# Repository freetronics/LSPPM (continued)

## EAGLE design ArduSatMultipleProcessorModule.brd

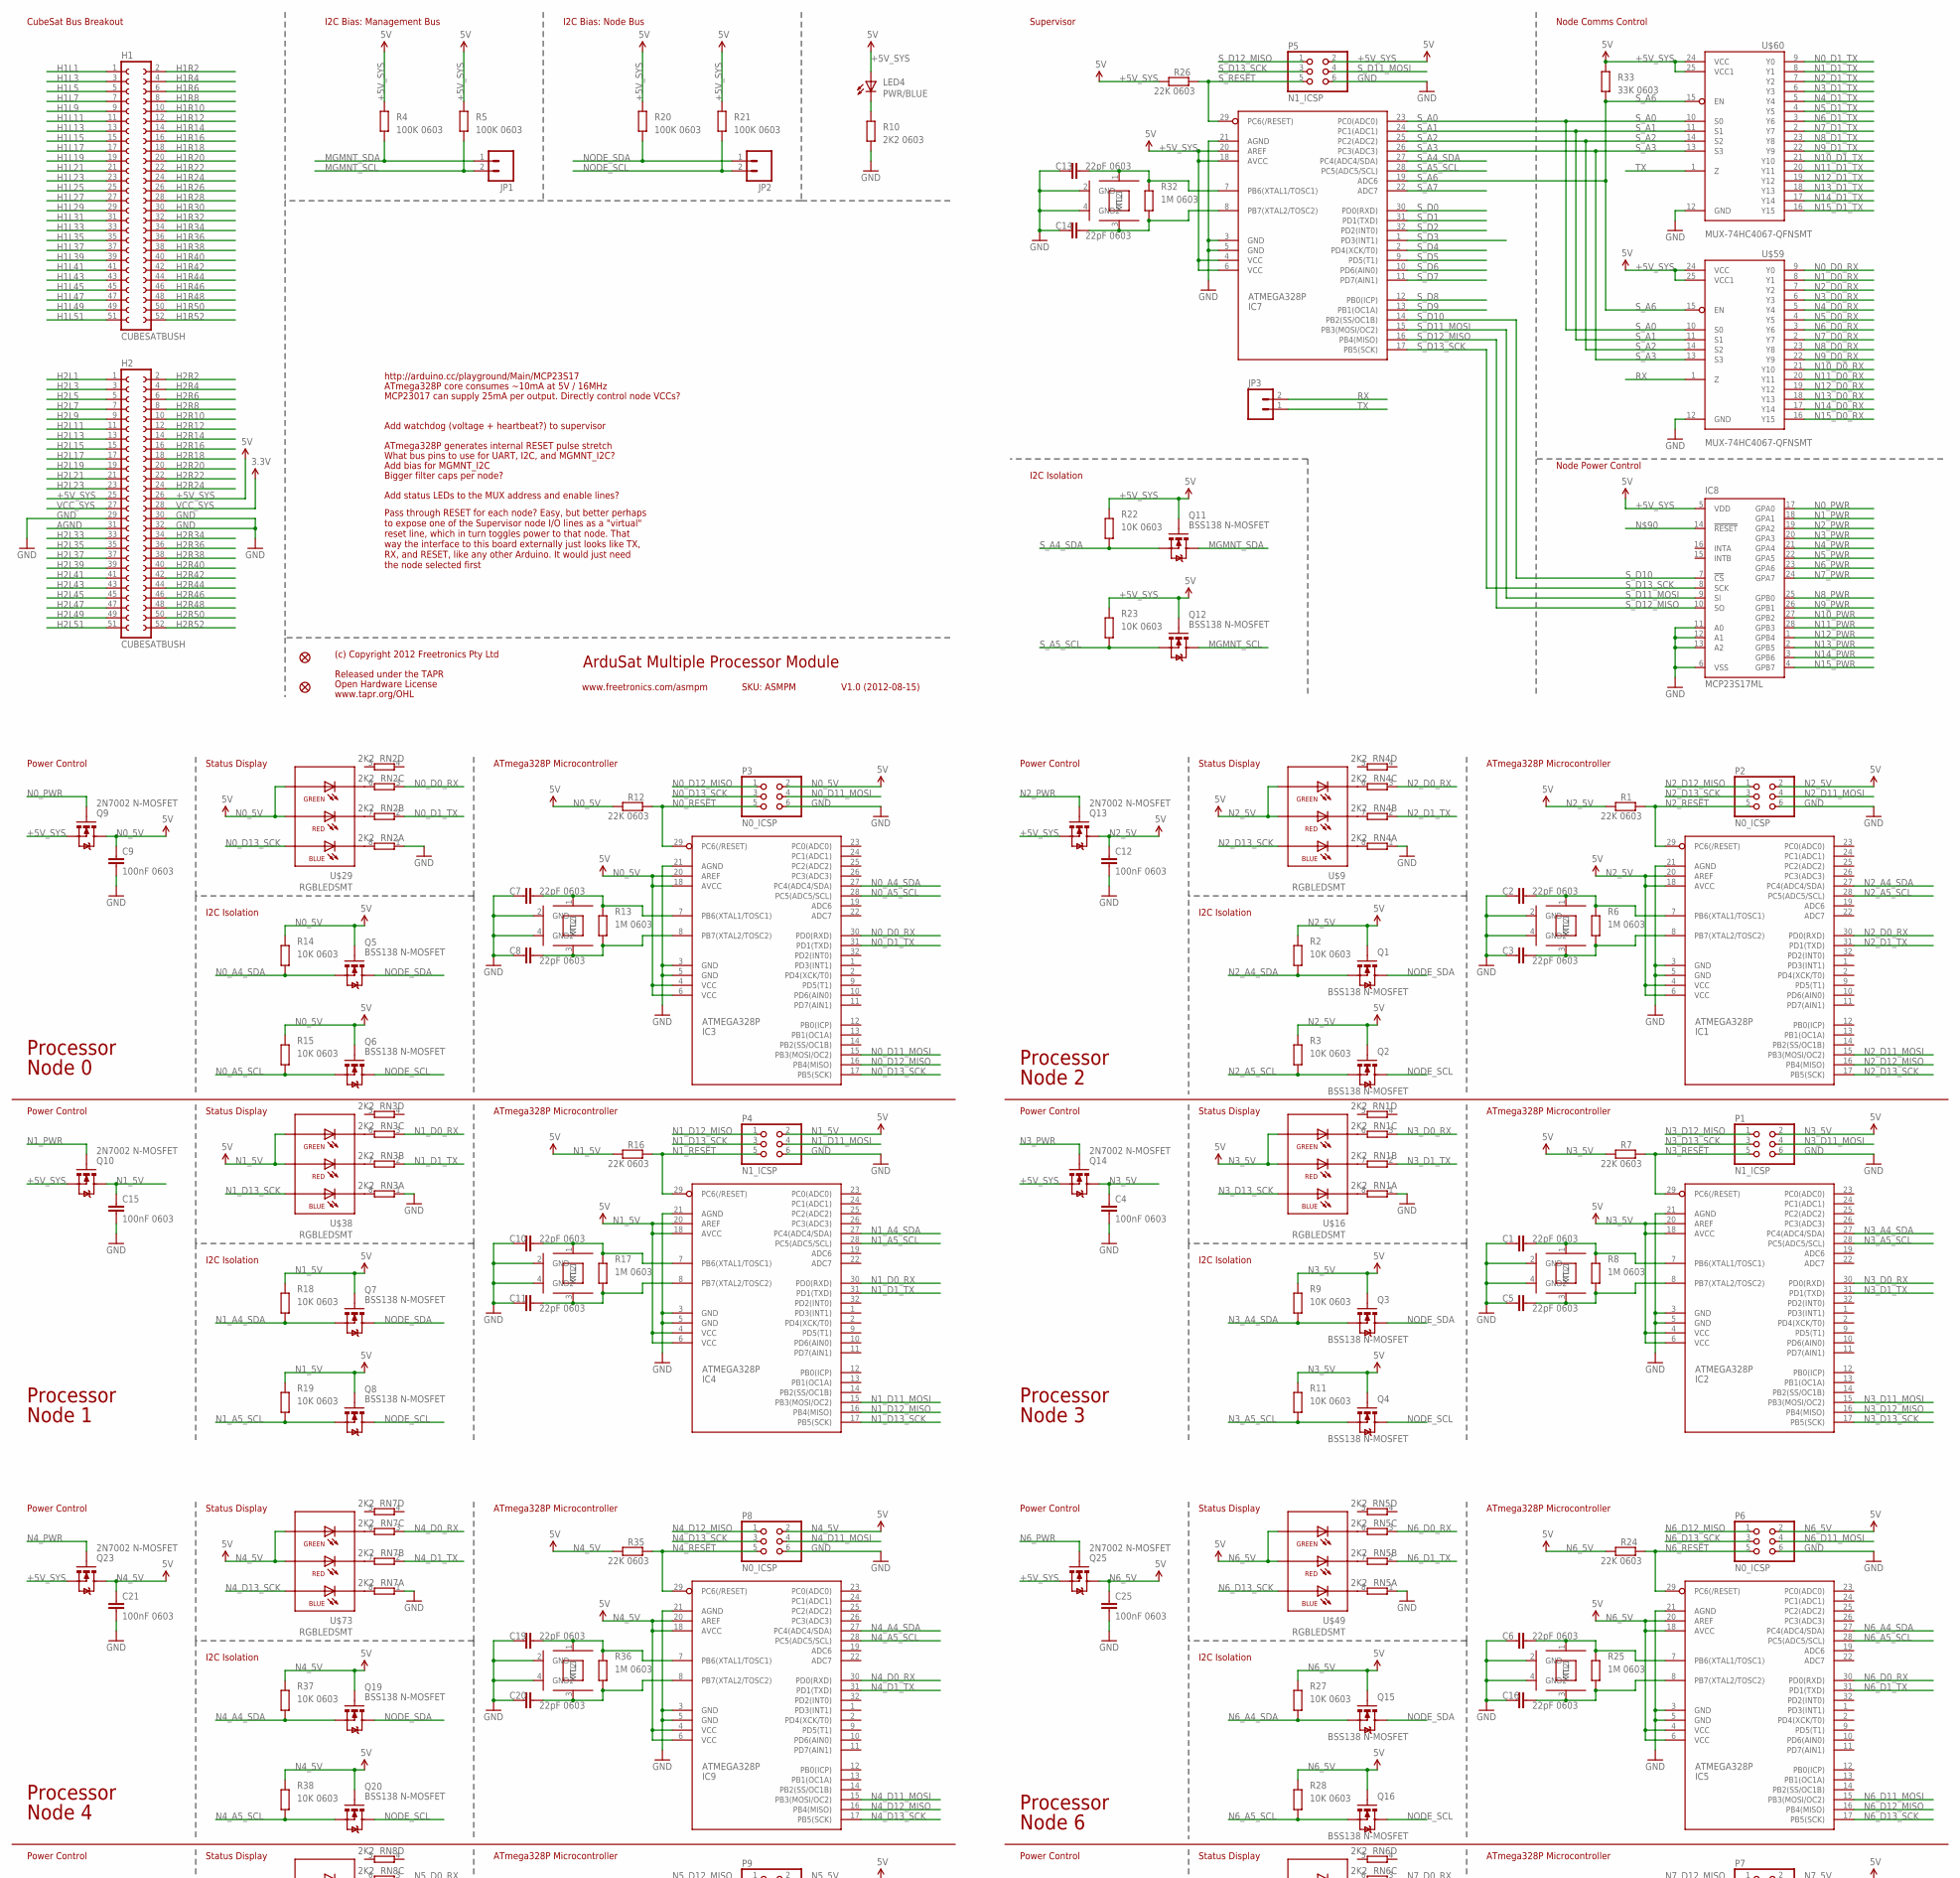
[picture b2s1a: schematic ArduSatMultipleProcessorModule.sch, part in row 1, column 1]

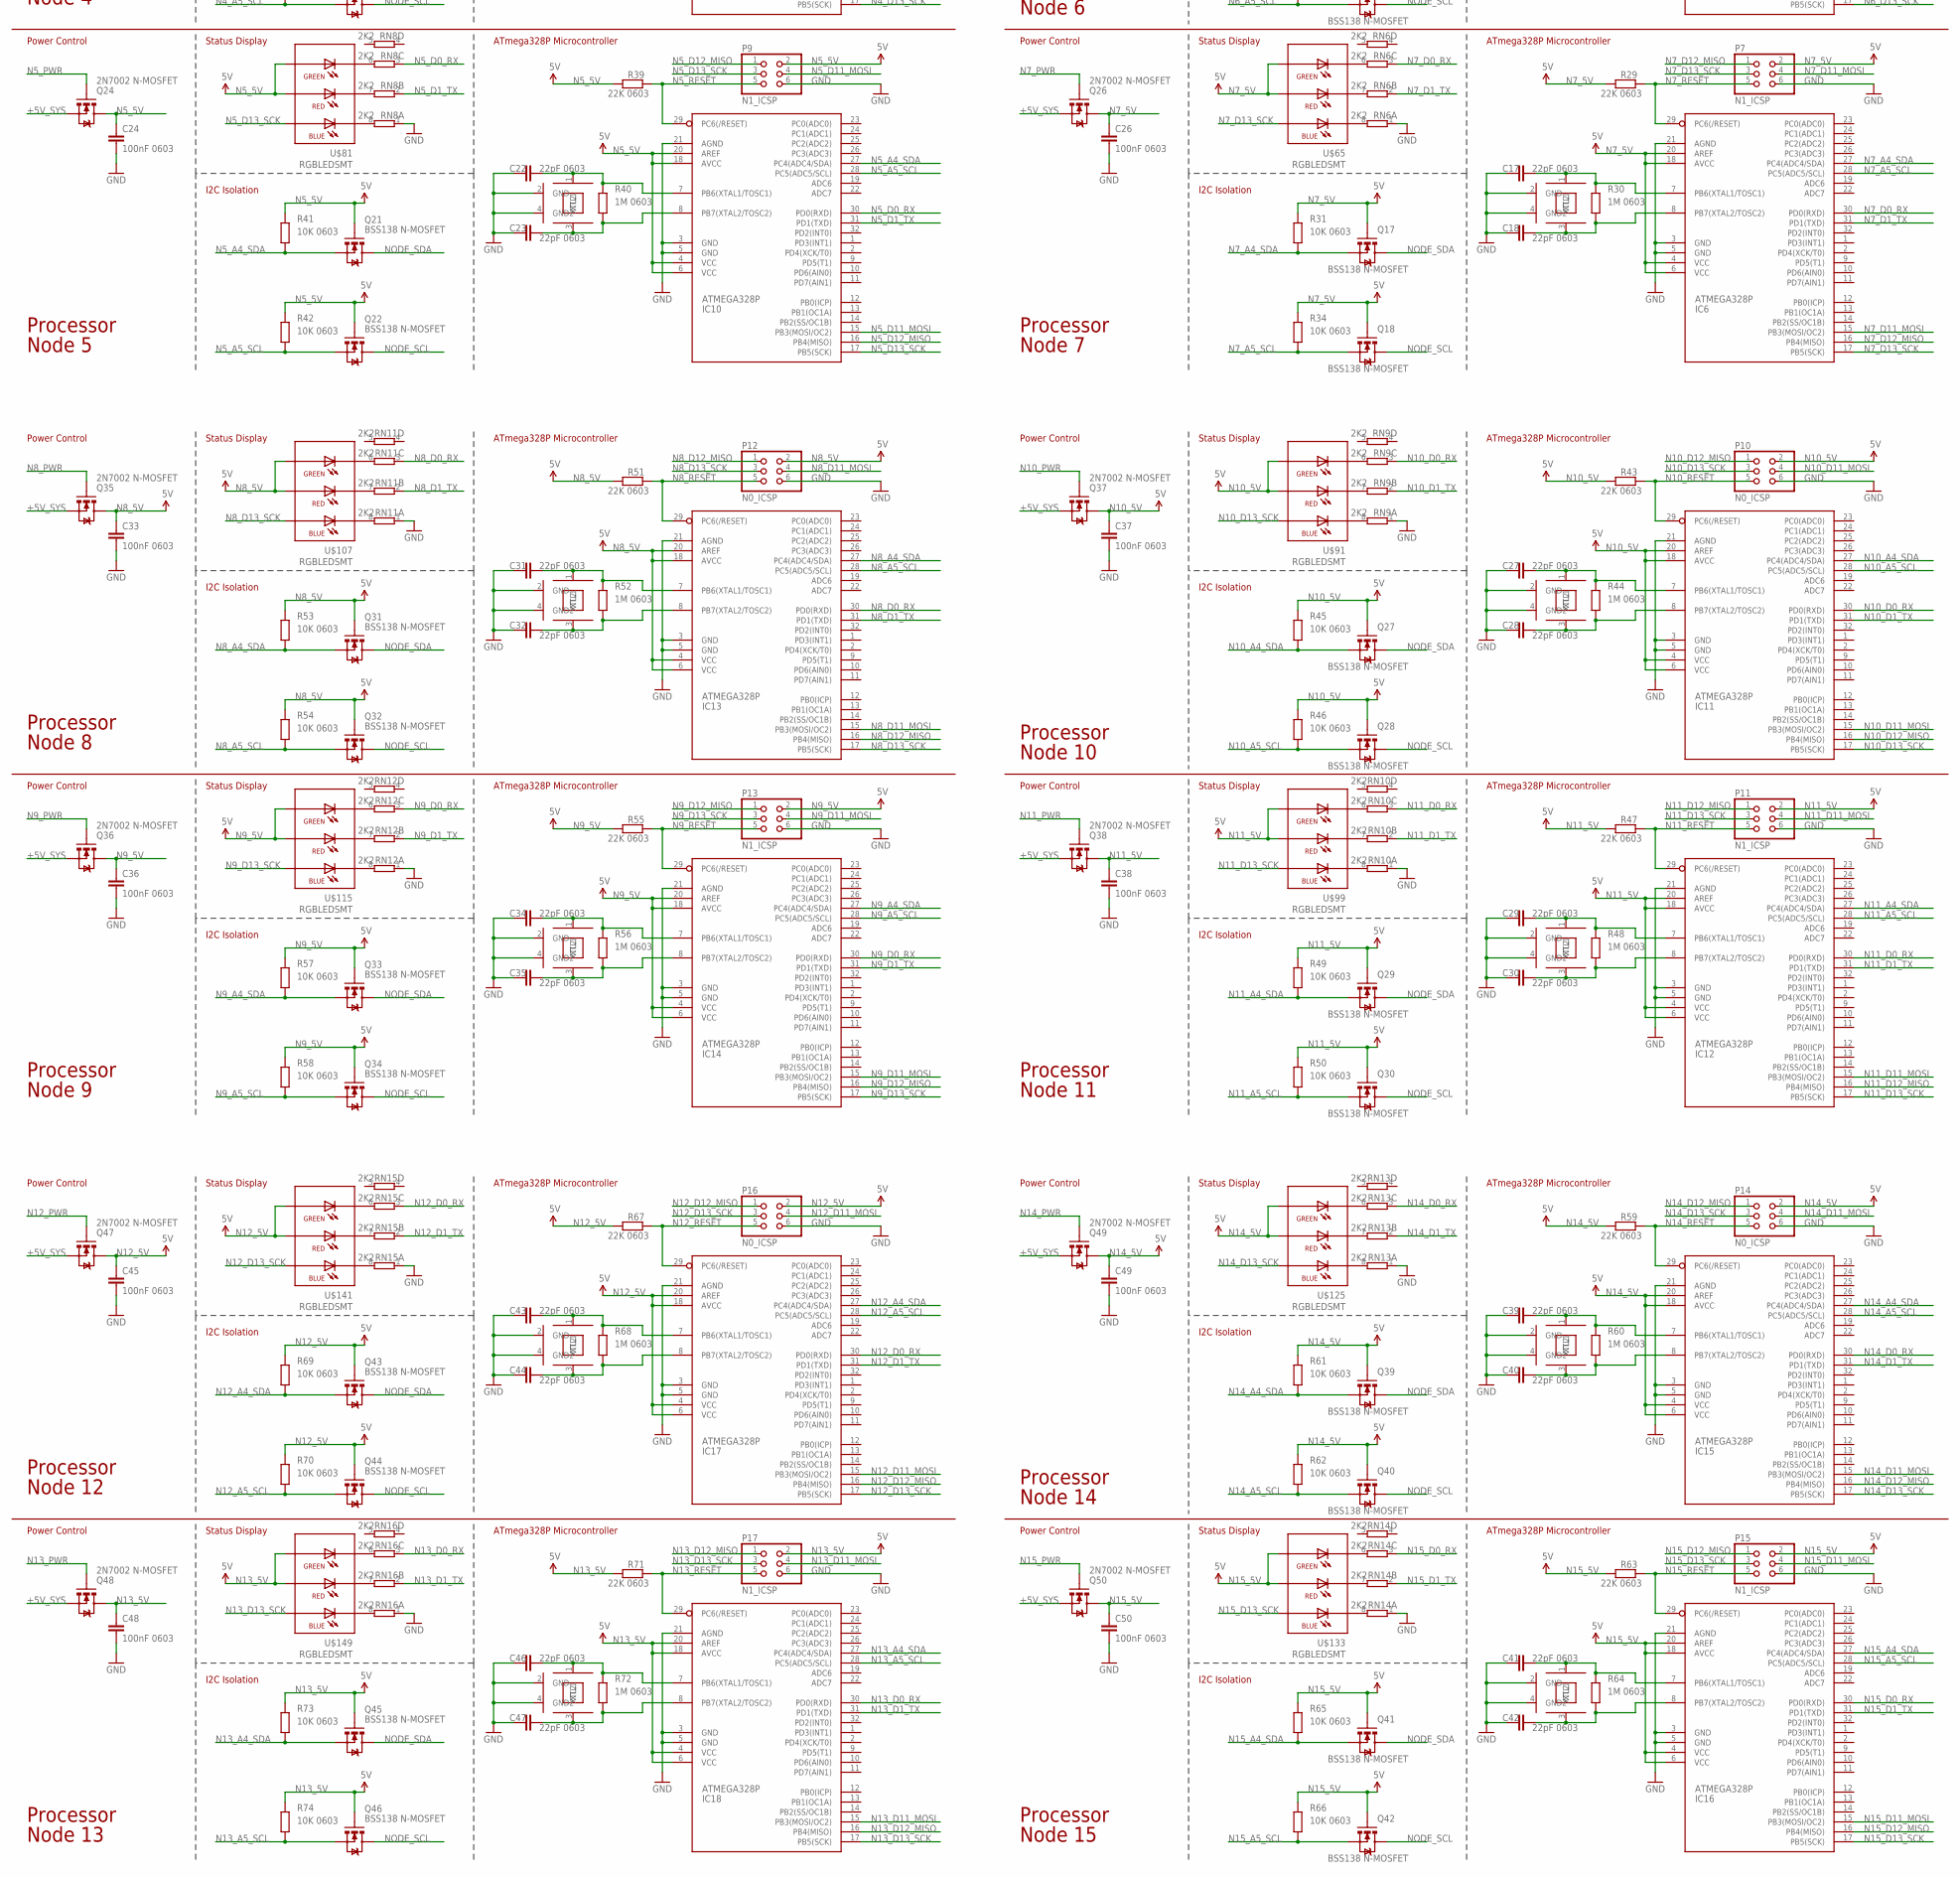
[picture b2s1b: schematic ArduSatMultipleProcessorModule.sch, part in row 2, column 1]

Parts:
C1, C2, C3, C5, C6, C7, C8, C10, C11, C13, C14, C16, C17, C18, C19, C20, C22, C23, C27, C28, C29, C30, C31, C32, C34, C35, C39, C40, C41, C42, C43, C44, C46, C47: 22pF 0603; 0603
C4, C9, C12, C15, C21, C24, C25, C26, C33, C36, C37, C38, C45, C48, C49, C50: 100nF 0603; 0603
H1, H2: CUBESATBUSH; CUBESATBUS
IC1, IC2, IC3, IC4, IC5, IC6, IC7, IC9, IC10, IC11, IC12, IC13, IC14, IC15, IC16, IC17, IC18: ATMEGA328P; MLF32
IC8: MCP23S17ML; QFN28-ML_6X6MM
JP1, JP2, JP3: M02PTH; 1X02
LED4: PWR/BLUE; LED-0603
P1, P4, P5, P7, P9, P11, P13, P15, P17: N1_ICSP; 2X03PTH
P2, P3, P6, P8, P10, P12, P14, P16: N0_ICSP; 2X03PTH
Q1, Q2, Q3, Q4, Q5, Q6, Q7, Q8, Q11, Q12, Q15, Q16, Q17, Q18, Q19, Q20, Q21, Q22, Q27, Q28, Q29, Q30, Q31, Q32, Q33, Q34, Q39, Q40, Q41, Q42, Q43, Q44, Q45, Q46: BSS138 N-MOSFET; SOT23-3
Q9, Q10, Q13, Q14, Q23, Q24, Q25, Q26, Q35, Q36, Q37, Q38, Q47, Q48, Q49, Q50: 2N7002 N-MOSFET; SOT23-3
R1, R7, R12, R16, R24, R26, R29, R35, R39, R43, R47, R51, R55, R59, R63, R67, R71: 22K 0603; 0603
R2, R3, R9, R11, R14, R15, R18, R19, R22, R23, R27, R28, R31, R34, R37, R38, R41, R42, R45, R46, R49, R50, R53, R54, R57, R58, R61, R62, R65, R66, R69, R70, R73, R74: 10K 0603; 0603
R4, R5, R20, R21: 100K 0603; 0603
R6, R8, R13, R17, R25, R30, R32, R36, R40, R44, R48, R52, R56, R60, R64, R68, R72: 1M 0603; 0603
R10: 2K2 0603; 0603
R33: 33K 0603; 0603
RN1, RN2, RN3, RN4, RN5, RN6, RN7, RN8, RN9, RN10, RN11, RN12, RN13, RN14, RN15, RN16: 2K2; CAY16
U$1, U$15, U$28, U$37, U$48, U$53, U$64, U$72, U$80, U$90, U$98, U$106, U$114, U$124, U$132, U$140, U$148: CRYSTAL-GND3X2; CRYSTAL-SMD-3X2
U$9, U$16, U$29, U$38, U$49, U$65, U$73, U$81, U$91, U$99, U$107, U$115, U$125, U$133, U$141, U$149: RGBLEDSMT; 19-337
U$21, U$22: FIDUCIAL1X2.5; FIDUCIAL-1X2.5
U$59, U$60: MUX-74HC4067-QFNSMT; DHVQFN24

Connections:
+5V_SYS: H2.25, H2.26, IC7.4 (VCC), IC7.6 (VCC), IC7.18 (AVCC), IC7.20 (AREF), IC8.5 (VDD), LED4.A, P5.2, Q9.2 (S), Q10.2 (S), Q11.1 (G), Q12.1 (G), Q13.2 (S), Q14.2 (S), Q23.2 (S), Q24.2 (S), Q25.2 (S), Q26.2 (S), Q35.2 (S), Q36.2 (S), Q37.2 (S), Q38.2 (S), Q47.2 (S), Q48.2 (S), Q49.2 (S), Q50.2 (S), R4.2, R5.2, R20.2, R21.2, R22.2, R23.2, R26.2, R33.2, U$59.24 (VCC), U$59.25 (VCC1), U$60.24 (VCC), U$60.25 (VCC1)
AGND: H2.31
GND: C1.1, C2.1, C3.1, C4.2, C5.1, C6.1, C7.1, C8.1, C9.2, C10.1, C11.1, C12.2, C13.1, C14.1, C15.2, C16.1, C17.1, C18.1, C19.1, C20.1, C21.2, C22.1, C23.1, C24.2, C25.2, C26.2, C27.1, C28.1, C29.1, C30.1, C31.1, C32.1, C33.2, C34.1, C35.1, C36.2, C37.2, C38.2, C39.1, C40.1, C41.1, C42.1, C43.1, C44.1, C45.2, C46.1, C47.1, C48.2, C49.2, C50.2, H2.29, H2.30, H2.32, IC1.3 (GND), IC1.5 (GND), IC1.21 (AGND), IC2.3 (GND), IC2.5 (GND), IC2.21 (AGND), IC3.3 (GND), IC3.5 (GND), IC3.21 (AGND), IC4.3 (GND), IC4.5 (GND), IC4.21 (AGND), IC5.3 (GND), IC5.5 (GND), IC5.21 (AGND), IC6.3 (GND), IC6.5 (GND), IC6.21 (AGND), IC7.3 (GND), IC7.5 (GND), IC7.21 (AGND), IC8.6 (VSS), IC8.11 (A0), IC8.12 (A1), IC8.13 (A2), IC9.3 (GND), IC9.5 (GND), IC9.21 (AGND), IC10.3 (GND), IC10.5 (GND), IC10.21 (AGND), IC11.3 (GND), IC11.5 (GND), IC11.21 (AGND), IC12.3 (GND), IC12.5 (GND), IC12.21 (AGND), IC13.3 (GND), IC13.5 (GND), IC13.21 (AGND), IC14.3 (GND), IC14.5 (GND), IC14.21 (AGND), IC15.3 (GND), IC15.5 (GND), IC15.21 (AGND), IC16.3 (GND), IC16.5 (GND), IC16.21 (AGND), IC17.3 (GND), IC17.5 (GND), IC17.21 (AGND), IC18.3 (GND), IC18.5 (GND), IC18.21 (AGND), P1.6, P2.6, P3.6, P4.6, P5.6, P6.6, P7.6, P8.6, P9.6, P10.6, P11.6, P12.6, P13.6, P14.6, P15.6, P16.6, P17.6, R10.1, RN1.1, RN2.1, RN3.1, RN4.1, RN5.1, RN6.1, RN7.1, RN8.1, RN9.1, RN10.1, RN11.1, RN12.1, RN13.1, RN14.1, RN15.1, RN16.1, U$1.2 (GND), U$1.4 (GND2), U$15.2 (GND), U$15.4 (GND2), U$28.2 (GND), U$28.4 (GND2), U$37.2 (GND), U$37.4 (GND2), U$48.2 (GND), U$48.4 (GND2), U$53.2 (GND), U$53.4 (GND2), U$59.12 (GND), U$60.12 (GND), U$64.2 (GND), U$64.4 (GND2), U$72.2 (GND), U$72.4 (GND2), U$80.2 (GND), U$80.4 (GND2), U$90.2 (GND), U$90.4 (GND2), U$98.2 (GND), U$98.4 (GND2), U$106.2 (GND), U$106.4 (GND2), U$114.2 (GND), U$114.4 (GND2), U$124.2 (GND), U$124.4 (GND2), U$132.2 (GND), U$132.4 (GND2), U$140.2 (GND), U$140.4 (GND2), U$148.2 (GND), U$148.4 (GND2)
H1L1: H1.1
H1L3: H1.3
H1L5: H1.5
H1L7: H1.7
H1L9: H1.9
H1L11: H1.11
H1L13: H1.13
H1L15: H1.15
H1L17: H1.17
H1L19: H1.19
H1L21: H1.21
H1L23: H1.23
H1L25: H1.25
H1L27: H1.27
H1L29: H1.29
H1L31: H1.31
H1L33: H1.33
H1L35: H1.35
H1L37: H1.37
H1L39: H1.39
H1L41: H1.41
H1L43: H1.43
H1L45: H1.45
H1L47: H1.47
H1L49: H1.49
H1L51: H1.51
H1R2: H1.2
H1R4: H1.4
H1R6: H1.6
H1R8: H1.8
H1R10: H1.10
H1R12: H1.12
H1R14: H1.14
H1R16: H1.16
H1R18: H1.18
H1R20: H1.20
H1R22: H1.22
H1R24: H1.24
H1R26: H1.26
H1R28: H1.28
H1R30: H1.30
H1R32: H1.32
H1R34: H1.34
H1R36: H1.36
H1R38: H1.38
H1R40: H1.40
H1R42: H1.42
H1R44: H1.44
H1R46: H1.46
H1R48: H1.48
H1R50: H1.50
H1R52: H1.52
H2L1: H2.1
H2L3: H2.3
H2L5: H2.5
H2L7: H2.7
H2L9: H2.9
H2L11: H2.11
H2L13: H2.13
H2L15: H2.15
H2L17: H2.17
H2L19: H2.19
H2L21: H2.21
H2L23: H2.23
H2L33: H2.33
H2L35: H2.35
H2L37: H2.37
H2L39: H2.39
H2L41: H2.41
H2L43: H2.43
H2L45: H2.45
H2L47: H2.47
H2L49: H2.49
H2L51: H2.51
H2R2: H2.2
H2R4: H2.4
H2R6: H2.6
H2R8: H2.8
H2R10: H2.10
H2R12: H2.12
H2R14: H2.14
H2R16: H2.16
H2R18: H2.18
H2R20: H2.20
H2R22: H2.22
H2R24: H2.24
H2R34: H2.34
H2R36: H2.36
H2R38: H2.38
H2R40: H2.40
H2R42: H2.42
H2R44: H2.44
H2R46: H2.46
H2R48: H2.48
H2R50: H2.50
H2R52: H2.52
MGMNT_SCL: JP1.2, Q12.3 (D), R5.1
MGMNT_SDA: JP1.1, Q11.3 (D), R4.1
N0_5V: C9.1, IC3.4 (VCC), IC3.6 (VCC), IC3.18 (AVCC), IC3.20 (AREF), P3.2, Q5.1 (G), Q6.1 (G), Q9.3 (D), R12.2, R14.2, R15.2, U$29.5 (A-R), U$29.6 (A-G)
N0_A4_SDA: IC3.27 (PC4(ADC4/SDA)), Q5.2 (S), R14.1
N0_A5_SCL: IC3.28 (PC5(ADC5/SCL)), Q6.2 (S), R15.1
N0_D0_RX: IC3.30 (PD0(RXD)), RN2.3 (1), U$59.9 (Y0)
N0_D1_TX: IC3.31 (PD1(TXD)), RN2.2 (1), U$60.9 (Y0)
N0_D11_MOSI: IC3.15 (PB3(MOSI/OC2)), P3.4
N0_D12_MISO: IC3.16 (PB4(MISO)), P3.1
N0_D13_SCK: IC3.17 (PB5(SCK)), P3.3, U$29.4 (A-B)
N0_PWR: IC8.17 (GPA0), Q9.1 (G)
N0_RESET: IC3.29 (PC6(/RESET)), P3.5, R12.1
N1_5V: C15.1, IC4.4 (VCC), IC4.6 (VCC), IC4.18 (AVCC), IC4.20 (AREF), P4.2, Q7.1 (G), Q8.1 (G), Q10.3 (D), R16.2, R18.2, R19.2, U$38.5 (A-R), U$38.6 (A-G)
N1_A4_SDA: IC4.27 (PC4(ADC4/SDA)), Q7.2 (S), R18.1
N1_A5_SCL: IC4.28 (PC5(ADC5/SCL)), Q8.2 (S), R19.1
N1_D0_RX: IC4.30 (PD0(RXD)), RN3.3 (1), U$59.8 (Y1)
N1_D1_TX: IC4.31 (PD1(TXD)), RN3.2 (1), U$60.8 (Y1)
N1_D11_MOSI: IC4.15 (PB3(MOSI/OC2)), P4.4
N1_D12_MISO: IC4.16 (PB4(MISO)), P4.1
N1_D13_SCK: IC4.17 (PB5(SCK)), P4.3, U$38.4 (A-B)
N1_PWR: IC8.18 (GPA1), Q10.1 (G)
N1_RESET: IC4.29 (PC6(/RESET)), P4.5, R16.1
N2_5V: C12.1, IC1.4 (VCC), IC1.6 (VCC), IC1.18 (AVCC), IC1.20 (AREF), P2.2, Q1.1 (G), Q2.1 (G), Q13.3 (D), R1.2, R2.2, R3.2, U$9.5 (A-R), U$9.6 (A-G)
N2_A4_SDA: IC1.27 (PC4(ADC4/SDA)), Q1.2 (S), R2.1
N2_A5_SCL: IC1.28 (PC5(ADC5/SCL)), Q2.2 (S), R3.1
N2_D0_RX: IC1.30 (PD0(RXD)), RN4.3 (1), U$59.7 (Y2)
N2_D1_TX: IC1.31 (PD1(TXD)), RN4.2 (1), U$60.7 (Y2)
N2_D11_MOSI: IC1.15 (PB3(MOSI/OC2)), P2.4
N2_D12_MISO: IC1.16 (PB4(MISO)), P2.1
N2_D13_SCK: IC1.17 (PB5(SCK)), P2.3, U$9.4 (A-B)
N2_PWR: IC8.19 (GPA2), Q13.1 (G)
N2_RESET: IC1.29 (PC6(/RESET)), P2.5, R1.1
N3_5V: C4.1, IC2.4 (VCC), IC2.6 (VCC), IC2.18 (AVCC), IC2.20 (AREF), P1.2, Q3.1 (G), Q4.1 (G), Q14.3 (D), R7.2, R9.2, R11.2, U$16.5 (A-R), U$16.6 (A-G)
N3_A4_SDA: IC2.27 (PC4(ADC4/SDA)), Q3.2 (S), R9.1
N3_A5_SCL: IC2.28 (PC5(ADC5/SCL)), Q4.2 (S), R11.1
N3_D0_RX: IC2.30 (PD0(RXD)), RN1.3 (1), U$59.6 (Y3)
N3_D1_TX: IC2.31 (PD1(TXD)), RN1.2 (1), U$60.6 (Y3)
N3_D11_MOSI: IC2.15 (PB3(MOSI/OC2)), P1.4
N3_D12_MISO: IC2.16 (PB4(MISO)), P1.1
N3_D13_SCK: IC2.17 (PB5(SCK)), P1.3, U$16.4 (A-B)
N3_PWR: IC8.20 (GPA3), Q14.1 (G)
N3_RESET: IC2.29 (PC6(/RESET)), P1.5, R7.1
N4_5V: C21.1, IC9.4 (VCC), IC9.6 (VCC), IC9.18 (AVCC), IC9.20 (AREF), P8.2, Q19.1 (G), Q20.1 (G), Q23.3 (D), R35.2, R37.2, R38.2, U$73.5 (A-R), U$73.6 (A-G)
N4_A4_SDA: IC9.27 (PC4(ADC4/SDA)), Q19.2 (S), R37.1
N4_A5_SCL: IC9.28 (PC5(ADC5/SCL)), Q20.2 (S), R38.1
N4_D0_RX: IC9.30 (PD0(RXD)), RN7.3 (1), U$59.5 (Y4)
N4_D1_TX: IC9.31 (PD1(TXD)), RN7.2 (1), U$60.5 (Y4)
N4_D11_MOSI: IC9.15 (PB3(MOSI/OC2)), P8.4
N4_D12_MISO: IC9.16 (PB4(MISO)), P8.1
N4_D13_SCK: IC9.17 (PB5(SCK)), P8.3, U$73.4 (A-B)
N4_PWR: IC8.21 (GPA4), Q23.1 (G)
N4_RESET: IC9.29 (PC6(/RESET)), P8.5, R35.1
N5_5V: C24.1, IC10.4 (VCC), IC10.6 (VCC), IC10.18 (AVCC), IC10.20 (AREF), P9.2, Q21.1 (G), Q22.1 (G), Q24.3 (D), R39.2, R41.2, R42.2, U$81.5 (A-R), U$81.6 (A-G)
N5_A4_SDA: IC10.27 (PC4(ADC4/SDA)), Q21.2 (S), R41.1
N5_A5_SCL: IC10.28 (PC5(ADC5/SCL)), Q22.2 (S), R42.1
N5_D0_RX: IC10.30 (PD0(RXD)), RN8.3 (1), U$59.4 (Y5)
N5_D1_TX: IC10.31 (PD1(TXD)), RN8.2 (1), U$60.4 (Y5)
N5_D11_MOSI: IC10.15 (PB3(MOSI/OC2)), P9.4
N5_D12_MISO: IC10.16 (PB4(MISO)), P9.1
N5_D13_SCK: IC10.17 (PB5(SCK)), P9.3, U$81.4 (A-B)
N5_PWR: IC8.22 (GPA5), Q24.1 (G)
N5_RESET: IC10.29 (PC6(/RESET)), P9.5, R39.1
N6_5V: C25.1, IC5.4 (VCC), IC5.6 (VCC), IC5.18 (AVCC), IC5.20 (AREF), P6.2, Q15.1 (G), Q16.1 (G), Q25.3 (D), R24.2, R27.2, R28.2, U$49.5 (A-R), U$49.6 (A-G)
N6_A4_SDA: IC5.27 (PC4(ADC4/SDA)), Q15.2 (S), R27.1
N6_A5_SCL: IC5.28 (PC5(ADC5/SCL)), Q16.2 (S), R28.1
N6_D0_RX: IC5.30 (PD0(RXD)), RN5.3 (1), U$59.3 (Y6)
N6_D1_TX: IC5.31 (PD1(TXD)), RN5.2 (1), U$60.3 (Y6)
N6_D11_MOSI: IC5.15 (PB3(MOSI/OC2)), P6.4
N6_D12_MISO: IC5.16 (PB4(MISO)), P6.1
N6_D13_SCK: IC5.17 (PB5(SCK)), P6.3, U$49.4 (A-B)
N6_PWR: IC8.23 (GPA6), Q25.1 (G)
N6_RESET: IC5.29 (PC6(/RESET)), P6.5, R24.1
N7_5V: C26.1, IC6.4 (VCC), IC6.6 (VCC), IC6.18 (AVCC), IC6.20 (AREF), P7.2, Q17.1 (G), Q18.1 (G), Q26.3 (D), R29.2, R31.2, R34.2, U$65.5 (A-R), U$65.6 (A-G)
N7_A4_SDA: IC6.27 (PC4(ADC4/SDA)), Q17.2 (S), R31.1
N7_A5_SCL: IC6.28 (PC5(ADC5/SCL)), Q18.2 (S), R34.1
N7_D0_RX: IC6.30 (PD0(RXD)), RN6.3 (1), U$59.2 (Y7)
N7_D1_TX: IC6.31 (PD1(TXD)), RN6.2 (1), U$60.2 (Y7)
N7_D11_MOSI: IC6.15 (PB3(MOSI/OC2)), P7.4
N7_D12_MISO: IC6.16 (PB4(MISO)), P7.1
N7_D13_SCK: IC6.17 (PB5(SCK)), P7.3, U$65.4 (A-B)
N7_PWR: IC8.24 (GPA7), Q26.1 (G)
N7_RESET: IC6.29 (PC6(/RESET)), P7.5, R29.1
N8_5V: C33.1, IC13.4 (VCC), IC13.6 (VCC), IC13.18 (AVCC), IC13.20 (AREF), P12.2, Q31.1 (G), Q32.1 (G), Q35.3 (D), R51.2, R53.2, R54.2, U$107.5 (A-R), U$107.6 (A-G)
N8_A4_SDA: IC13.27 (PC4(ADC4/SDA)), Q31.2 (S), R53.1
N8_A5_SCL: IC13.28 (PC5(ADC5/SCL)), Q32.2 (S), R54.1
N8_D0_RX: IC13.30 (PD0(RXD)), RN11.3 (1), U$59.23 (Y8)
N8_D1_TX: IC13.31 (PD1(TXD)), RN11.2 (1), U$60.23 (Y8)
N8_D11_MOSI: IC13.15 (PB3(MOSI/OC2)), P12.4
N8_D12_MISO: IC13.16 (PB4(MISO)), P12.1
N8_D13_SCK: IC13.17 (PB5(SCK)), P12.3, U$107.4 (A-B)
N8_PWR: IC8.25 (GPB0), Q35.1 (G)
N8_RESET: IC13.29 (PC6(/RESET)), P12.5, R51.1
N9_5V: C36.1, IC14.4 (VCC), IC14.6 (VCC), IC14.18 (AVCC), IC14.20 (AREF), P13.2, Q33.1 (G), Q34.1 (G), Q36.3 (D), R55.2, R57.2, R58.2, U$115.5 (A-R), U$115.6 (A-G)
N9_A4_SDA: IC14.27 (PC4(ADC4/SDA)), Q33.2 (S), R57.1
N9_A5_SCL: IC14.28 (PC5(ADC5/SCL)), Q34.2 (S), R58.1
N9_D0_RX: IC14.30 (PD0(RXD)), RN12.3 (1), U$59.22 (Y9)
N9_D1_TX: IC14.31 (PD1(TXD)), RN12.2 (1), U$60.22 (Y9)
N9_D11_MOSI: IC14.15 (PB3(MOSI/OC2)), P13.4
N9_D12_MISO: IC14.16 (PB4(MISO)), P13.1
N9_D13_SCK: IC14.17 (PB5(SCK)), P13.3, U$115.4 (A-B)
N9_PWR: IC8.26 (GPB1), Q36.1 (G)
N9_RESET: IC14.29 (PC6(/RESET)), P13.5, R55.1
N10_5V: C37.1, IC11.4 (VCC), IC11.6 (VCC), IC11.18 (AVCC), IC11.20 (AREF), P10.2, Q27.1 (G), Q28.1 (G), Q37.3 (D), R43.2, R45.2, R46.2, U$91.5 (A-R), U$91.6 (A-G)
N10_A4_SDA: IC11.27 (PC4(ADC4/SDA)), Q27.2 (S), R45.1
N10_A5_SCL: IC11.28 (PC5(ADC5/SCL)), Q28.2 (S), R46.1
N10_D0_RX: IC11.30 (PD0(RXD)), RN9.3 (1), U$59.21 (Y10)
N10_D1_TX: IC11.31 (PD1(TXD)), RN9.2 (1), U$60.21 (Y10)
N10_D11_MOSI: IC11.15 (PB3(MOSI/OC2)), P10.4
N10_D12_MISO: IC11.16 (PB4(MISO)), P10.1
N10_D13_SCK: IC11.17 (PB5(SCK)), P10.3, U$91.4 (A-B)
N10_PWR: IC8.27 (GPB2), Q37.1 (G)
N10_RESET: IC11.29 (PC6(/RESET)), P10.5, R43.1
N11_5V: C38.1, IC12.4 (VCC), IC12.6 (VCC), IC12.18 (AVCC), IC12.20 (AREF), P11.2, Q29.1 (G), Q30.1 (G), Q38.3 (D), R47.2, R49.2, R50.2, U$99.5 (A-R), U$99.6 (A-G)
N11_A4_SDA: IC12.27 (PC4(ADC4/SDA)), Q29.2 (S), R49.1
N11_A5_SCL: IC12.28 (PC5(ADC5/SCL)), Q30.2 (S), R50.1
N11_D0_RX: IC12.30 (PD0(RXD)), RN10.3 (1), U$59.20 (Y11)
N11_D1_TX: IC12.31 (PD1(TXD)), RN10.2 (1), U$60.20 (Y11)
N11_D11_MOSI: IC12.15 (PB3(MOSI/OC2)), P11.4
N11_D12_MISO: IC12.16 (PB4(MISO)), P11.1
N11_D13_SCK: IC12.17 (PB5(SCK)), P11.3, U$99.4 (A-B)
N11_PWR: IC8.28 (GPB3), Q38.1 (G)
N11_RESET: IC12.29 (PC6(/RESET)), P11.5, R47.1
N12_5V: C45.1, IC17.4 (VCC), IC17.6 (VCC), IC17.18 (AVCC), IC17.20 (AREF), P16.2, Q43.1 (G), Q44.1 (G), Q47.3 (D), R67.2, R69.2, R70.2, U$141.5 (A-R), U$141.6 (A-G)
N12_A4_SDA: IC17.27 (PC4(ADC4/SDA)), Q43.2 (S), R69.1
N12_A5_SCL: IC17.28 (PC5(ADC5/SCL)), Q44.2 (S), R70.1
N12_D0_RX: IC17.30 (PD0(RXD)), RN15.3 (1), U$59.19 (Y12)
N12_D1_TX: IC17.31 (PD1(TXD)), RN15.2 (1), U$60.19 (Y12)
N12_D11_MOSI: IC17.15 (PB3(MOSI/OC2)), P16.4
N12_D12_MISO: IC17.16 (PB4(MISO)), P16.1
N12_D13_SCK: IC17.17 (PB5(SCK)), P16.3, U$141.4 (A-B)
N12_PWR: IC8.1 (GPB4), Q47.1 (G)
N12_RESET: IC17.29 (PC6(/RESET)), P16.5, R67.1
N13_5V: C48.1, IC18.4 (VCC), IC18.6 (VCC), IC18.18 (AVCC), IC18.20 (AREF), P17.2, Q45.1 (G), Q46.1 (G), Q48.3 (D), R71.2, R73.2, R74.2, U$149.5 (A-R), U$149.6 (A-G)
N13_A4_SDA: IC18.27 (PC4(ADC4/SDA)), Q45.2 (S), R73.1
N13_A5_SCL: IC18.28 (PC5(ADC5/SCL)), Q46.2 (S), R74.1
N13_D0_RX: IC18.30 (PD0(RXD)), RN16.3 (1), U$59.18 (Y13)
N13_D1_TX: IC18.31 (PD1(TXD)), RN16.2 (1), U$60.18 (Y13)
N13_D11_MOSI: IC18.15 (PB3(MOSI/OC2)), P17.4
N13_D12_MISO: IC18.16 (PB4(MISO)), P17.1
N13_D13_SCK: IC18.17 (PB5(SCK)), P17.3, U$149.4 (A-B)
N13_PWR: IC8.2 (GPB5), Q48.1 (G)
N13_RESET: IC18.29 (PC6(/RESET)), P17.5, R71.1
N14_5V: C49.1, IC15.4 (VCC), IC15.6 (VCC), IC15.18 (AVCC), IC15.20 (AREF), P14.2, Q39.1 (G), Q40.1 (G), Q49.3 (D), R59.2, R61.2, R62.2, U$125.5 (A-R), U$125.6 (A-G)
N14_A4_SDA: IC15.27 (PC4(ADC4/SDA)), Q39.2 (S), R61.1
N14_A5_SCL: IC15.28 (PC5(ADC5/SCL)), Q40.2 (S), R62.1
N14_D0_RX: IC15.30 (PD0(RXD)), RN13.3 (1), U$59.17 (Y14)
N14_D1_TX: IC15.31 (PD1(TXD)), RN13.2 (1), U$60.17 (Y14)
N14_D11_MOSI: IC15.15 (PB3(MOSI/OC2)), P14.4
N14_D12_MISO: IC15.16 (PB4(MISO)), P14.1
N14_D13_SCK: IC15.17 (PB5(SCK)), P14.3, U$125.4 (A-B)
N14_PWR: IC8.3 (GPB6), Q49.1 (G)
N14_RESET: IC15.29 (PC6(/RESET)), P14.5, R59.1
N15_5V: C50.1, IC16.4 (VCC), IC16.6 (VCC), IC16.18 (AVCC), IC16.20 (AREF), P15.2, Q41.1 (G), Q42.1 (G), Q50.3 (D), R63.2, R65.2, R66.2, U$133.5 (A-R), U$133.6 (A-G)
N15_A4_SDA: IC16.27 (PC4(ADC4/SDA)), Q41.2 (S), R65.1
N15_A5_SCL: IC16.28 (PC5(ADC5/SCL)), Q42.2 (S), R66.1
N15_D0_RX: IC16.30 (PD0(RXD)), RN14.3 (1), U$59.16 (Y15)
N15_D1_TX: IC16.31 (PD1(TXD)), RN14.2 (1), U$60.16 (Y15)
N15_D11_MOSI: IC16.15 (PB3(MOSI/OC2)), P15.4
N15_D12_MISO: IC16.16 (PB4(MISO)), P15.1
N15_D13_SCK: IC16.17 (PB5(SCK)), P15.3, U$133.4 (A-B)
N15_PWR: IC8.4 (GPB7), Q50.1 (G)
N15_RESET: IC16.29 (PC6(/RESET)), P15.5, R63.1
unnamed: C5.2, IC2.8 (PB7(XTAL2/TOSC2)), R8.1, U$15.3 (XTL2)
unnamed: C2.2, IC1.7 (PB6(XTAL1/TOSC1)), R6.2, U$1.1 (XTL1)
unnamed: C1.2, IC2.7 (PB6(XTAL1/TOSC1)), R8.2, U$15.1 (XTL1)
unnamed: RN4.6 (2), U$9.3 (C-G)
unnamed: RN4.7 (2), U$9.2 (C-R)
unnamed: RN4.8 (2), U$9.1 (C-B)
unnamed: C3.2, IC1.8 (PB7(XTAL2/TOSC2)), R6.1, U$1.3 (XTL2)
unnamed: RN1.6 (2), U$16.3 (C-G)
unnamed: RN1.7 (2), U$16.2 (C-R)
unnamed: RN1.8 (2), U$16.1 (C-B)
unnamed: C8.2, IC3.8 (PB7(XTAL2/TOSC2)), R13.1, U$28.3 (XTL2)
unnamed: C7.2, IC3.7 (PB6(XTAL1/TOSC1)), R13.2, U$28.1 (XTL1)
unnamed: RN2.7 (2), U$29.2 (C-R)
unnamed: LED4.C, R10.2
unnamed: RN2.6 (2), U$29.3 (C-G)
unnamed: RN2.8 (2), U$29.1 (C-B)
unnamed: C11.2, IC4.8 (PB7(XTAL2/TOSC2)), R17.1, U$37.3 (XTL2)
unnamed: C10.2, IC4.7 (PB6(XTAL1/TOSC1)), R17.2, U$37.1 (XTL1)
unnamed: RN3.6 (2), U$38.3 (C-G)
unnamed: RN3.7 (2), U$38.2 (C-R)
unnamed: RN3.8 (2), U$38.1 (C-B)
unnamed: C14.2, IC7.8 (PB7(XTAL2/TOSC2)), R32.1, U$53.3 (XTL2)
unnamed: C13.2, IC7.7 (PB6(XTAL1/TOSC1)), R32.2, U$53.1 (XTL1)
unnamed: C16.2, IC5.8 (PB7(XTAL2/TOSC2)), R25.1, U$48.3 (XTL2)
unnamed: C6.2, IC5.7 (PB6(XTAL1/TOSC1)), R25.2, U$48.1 (XTL1)
unnamed: RN5.6 (2), U$49.3 (C-G)
unnamed: RN5.7 (2), U$49.2 (C-R)
unnamed: RN5.8 (2), U$49.1 (C-B)
unnamed: C18.2, IC6.8 (PB7(XTAL2/TOSC2)), R30.1, U$64.3 (XTL2)
unnamed: C17.2, IC6.7 (PB6(XTAL1/TOSC1)), R30.2, U$64.1 (XTL1)
unnamed: RN6.6 (2), U$65.3 (C-G)
unnamed: RN6.7 (2), U$65.2 (C-R)
unnamed: RN6.8 (2), U$65.1 (C-B)
unnamed: C20.2, IC9.8 (PB7(XTAL2/TOSC2)), R36.1, U$72.3 (XTL2)
unnamed: C19.2, IC9.7 (PB6(XTAL1/TOSC1)), R36.2, U$72.1 (XTL1)
unnamed: C23.2, IC10.8 (PB7(XTAL2/TOSC2)), R40.1, U$80.3 (XTL2)
unnamed: C22.2, IC10.7 (PB6(XTAL1/TOSC1)), R40.2, U$80.1 (XTL1)
unnamed: RN8.8 (2), U$81.1 (C-B)
unnamed: RN8.6 (2), U$81.3 (C-G)
unnamed: RN8.7 (2), U$81.2 (C-R)
unnamed: RN7.7 (2), U$73.2 (C-R)
unnamed: RN7.6 (2), U$73.3 (C-G)
unnamed: RN7.8 (2), U$73.1 (C-B)
unnamed: C28.2, IC11.8 (PB7(XTAL2/TOSC2)), R44.1, U$90.3 (XTL2)
unnamed: C27.2, IC11.7 (PB6(XTAL1/TOSC1)), R44.2, U$90.1 (XTL1)
unnamed: C30.2, IC12.8 (PB7(XTAL2/TOSC2)), R48.1, U$98.3 (XTL2)
unnamed: C29.2, IC12.7 (PB6(XTAL1/TOSC1)), R48.2, U$98.1 (XTL1)
unnamed: C32.2, IC13.8 (PB7(XTAL2/TOSC2)), R52.1, U$106.3 (XTL2)
unnamed: C31.2, IC13.7 (PB6(XTAL1/TOSC1)), R52.2, U$106.1 (XTL1)
unnamed: C35.2, IC14.8 (PB7(XTAL2/TOSC2)), R56.1, U$114.3 (XTL2)
unnamed: C34.2, IC14.7 (PB6(XTAL1/TOSC1)), R56.2, U$114.1 (XTL1)
unnamed: RN12.8 (2), U$115.1 (C-B)
unnamed: RN12.6 (2), U$115.3 (C-G)
unnamed: RN12.7 (2), U$115.2 (C-R)
unnamed: RN11.7 (2), U$107.2 (C-R)
unnamed: RN11.6 (2), U$107.3 (C-G)
unnamed: RN11.8 (2), U$107.1 (C-B)
unnamed: C40.2, IC15.8 (PB7(XTAL2/TOSC2)), R60.1, U$124.3 (XTL2)
unnamed: C39.2, IC15.7 (PB6(XTAL1/TOSC1)), R60.2, U$124.1 (XTL1)
unnamed: C42.2, IC16.8 (PB7(XTAL2/TOSC2)), R64.1, U$132.3 (XTL2)
unnamed: C41.2, IC16.7 (PB6(XTAL1/TOSC1)), R64.2, U$132.1 (XTL1)
unnamed: C44.2, IC17.8 (PB7(XTAL2/TOSC2)), R68.1, U$140.3 (XTL2)
unnamed: C43.2, IC17.7 (PB6(XTAL1/TOSC1)), R68.2, U$140.1 (XTL1)
unnamed: C47.2, IC18.8 (PB7(XTAL2/TOSC2)), R72.1, U$148.3 (XTL2)
unnamed: C46.2, IC18.7 (PB6(XTAL1/TOSC1)), R72.2, U$148.1 (XTL1)
unnamed: RN16.8 (2), U$149.1 (C-B)
unnamed: RN16.6 (2), U$149.3 (C-G)
unnamed: RN16.7 (2), U$149.2 (C-R)
unnamed: RN15.7 (2), U$141.2 (C-R)
unnamed: RN15.6 (2), U$141.3 (C-G)
unnamed: RN15.8 (2), U$141.1 (C-B)
unnamed: RN9.6 (2), U$91.3 (C-G)
unnamed: RN9.7 (2), U$91.2 (C-R)
unnamed: RN9.8 (2), U$91.1 (C-B)
unnamed: RN10.6 (2), U$99.3 (C-G)
unnamed: RN10.7 (2), U$99.2 (C-R)
unnamed: RN10.8 (2), U$99.1 (C-B)
unnamed: RN13.6 (2), U$125.3 (C-G)
unnamed: RN13.7 (2), U$125.2 (C-R)
unnamed: RN13.8 (2), U$125.1 (C-B)
unnamed: RN14.6 (2), U$133.3 (C-G)
unnamed: RN14.7 (2), U$133.2 (C-R)
unnamed: RN14.8 (2), U$133.1 (C-B)
NODE_SCL: JP2.2, Q2.3 (D), Q4.3 (D), Q6.3 (D), Q8.3 (D), Q16.3 (D), Q18.3 (D), Q20.3 (D), Q22.3 (D), Q28.3 (D), Q30.3 (D), Q32.3 (D), Q34.3 (D), Q40.3 (D), Q42.3 (D), Q44.3 (D), Q46.3 (D), R21.1
NODE_SDA: JP2.1, Q1.3 (D), Q3.3 (D), Q5.3 (D), Q7.3 (D), Q15.3 (D), Q17.3 (D), Q19.3 (D), Q21.3 (D), Q27.3 (D), Q29.3 (D), Q31.3 (D), Q33.3 (D), Q39.3 (D), Q41.3 (D), Q43.3 (D), Q45.3 (D), R20.1
RX: JP3.2, U$59.1 (Z)
S_A0: IC7.23 (PC0(ADC0)), U$59.10 (S0), U$60.10 (S0)
S_A1: IC7.24 (PC1(ADC1)), U$59.11 (S1), U$60.11 (S1)
S_A2: IC7.25 (PC2(ADC2)), U$59.14 (S2), U$60.14 (S2)
S_A3: IC7.26 (PC3(ADC3)), U$59.13 (S3), U$60.13 (S3)
S_A4_SDA: IC7.27 (PC4(ADC4/SDA)), Q11.2 (S), R22.1
S_A5_SCL: IC7.28 (PC5(ADC5/SCL)), Q12.2 (S), R23.1
S_A6: IC7.19 (ADC6), R33.1, U$59.15 (EN), U$60.15 (EN)
S_A7: IC7.22 (ADC7)
S_D0: IC7.30 (PD0(RXD))
S_D1: IC7.31 (PD1(TXD))
S_D2: IC7.32 (PD2(INT0))
S_D3: IC7.1 (PD3(INT1))
S_D4: IC7.2 (PD4(XCK/T0))
S_D5: IC7.9 (PD5(T1))
S_D6: IC7.10 (PD6(AIN0))
S_D7: IC7.11 (PD7(AIN1))
S_D8: IC7.12 (PB0(ICP))
S_D9: IC7.13 (PB1(OC1A))
S_D10: IC7.14 (PB2(SS/OC1B)), IC8.7 (!CS)
S_D11_MOSI: IC7.15 (PB3(MOSI/OC2)), IC8.9 (SI), P5.4
S_D12_MISO: IC7.16 (PB4(MISO)), IC8.10 (SO), P5.1
S_D13_SCK: IC7.17 (PB5(SCK)), IC8.8 (SCK), P5.3
S_RESET: IC7.29 (PC6(/RESET)), P5.5, R26.1
TX: JP3.1, U$60.1 (Z)
VCC_SYS: H2.27, H2.28

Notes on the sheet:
ArduSat Multiple Processor Module
V1.0 (2012-08-15)
www.freetronics.com/asmpm
SKU: ASMPM
CubeSat Bus Breakout
Released under the TAPR
Open Hardware License
www.tapr.org/OHL
(c) Copyright 2012 Freetronics Pty Ltd
ATmega328P Microcontroller
I2C Isolation
Status Display
Processor
MCP23017 can supply 25mA per output. Directly control node VCCs?
I2C Bias: Management Bus
What bus pins to use for UART, I2C, and MGMNT_I2C?
Add bias for MGMNT_I2C
Bigger filter caps per node?
ATmega328P generates internal RESET pulse stretch
Supervisor
ATmega328P core consumes ~10mA at 5V / 16MHz
Node Comms Control
Add watchdog (voltage + heartbeat?) to supervisor
Power Control
Node 0
Node 1
Pass through RESET for each node? Easy, but better perhaps to expose one of the Supervisor node I/O lines as a "virtual" reset line, which in turn toggles power to that node. That way the interface to this board externally just looks like TX, RX, and RESET, like any other Arduino. It would just nee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
Node Power Control
http://arduino.cc/playground/Main/MCP23S17
I2C Bias: Node Bus
Add status LEDs to the MUX address and enable lines?
Node 2
Node 4
Node 5
Node 6
Node 3
Node 7
Node 8
Node 9
Node 10

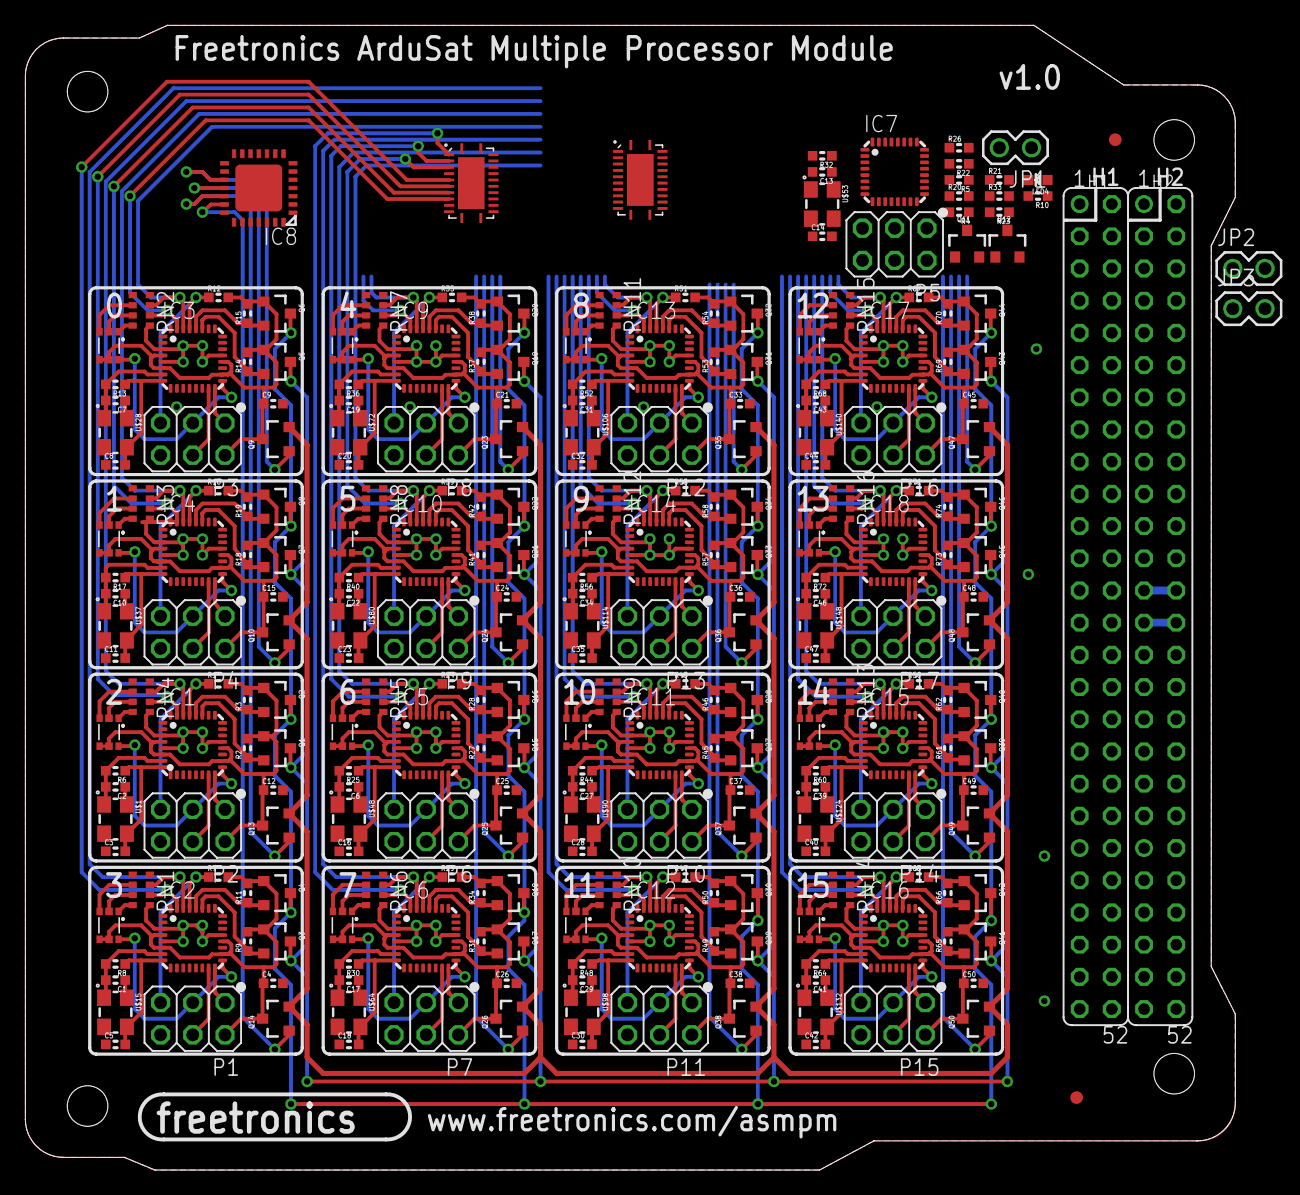
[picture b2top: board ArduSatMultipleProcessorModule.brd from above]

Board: 2 copper layers, 95.5 x 90.3 mm, 268 parts (0 on the bottom side), 264 nets.

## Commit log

2012-11-29 Initial project import
2012-11-29 Testing replacement of latches using ATmega328
2012-11-30 Added alternative supervisor node
2012-12-02 Added VCC control for nodes 0 and 1
2012-12-03 Supervisor now has control of both node power and serial comms
2012-12-03 Removed direct control option for UART MUX and power
2012-12-03 Experiments with node layout
2012-12-03 Experiments in node dimensions and layout
2012-12-04 Added parts for remaining nodes
2012-12-05 Routing processor nodes
2012-12-06 Routing
2012-12-08 Moved nodes back down to lower part of module
2012-12-08 Experiments with arrangements of UART and PWR control
2013-01-05 Restructured project as payload module with duplicated payload nodes
2013-01-05 Deleted old project files
2013-01-08 Placement and routing
2013-01-08 Renamed project files
2013-01-08 Updated Eagle project file
2013-01-10 ERC and DRC for production
2013-01-17 Fix footprint for RGB LED
2013-02-14 Fixed ISP pin assignment Added D13 LED to supervisor Fixed TX/RX from supervisor to multiplexers Replaced 4-pin debug connector with 6-pin connector in FTDI-type format Linked supervisor reset to deb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
2013-02-16 Added labels for power source selection jumpers; added parts for node reset latch
2013-02-16 Start of placement and fan-out of node reset latch
2013-02-17 Finished routing latch for resetting nodes
2013-02-17 Clearance and label improvements
2013-02-18 Re-routed around MCU GND pads and improved footprints
2013-02-18 Clearances and DRC for v1.1 release
2013-02-18 Switched PWR LED to 0402
2013-02-21 Release 1.2: power jumpers on TMP102s; clearances
2013-02-21 Added PDF of schematic
2017-08-24 Updated README and board files for public release
2017-08-24 Removed obsolete docs folder from template project
2019-09-01 Replaced most parts using SuperHouse library to add 3D models
